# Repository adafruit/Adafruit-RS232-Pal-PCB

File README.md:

## Adafruit RS232 Pal - Two Channel UART to RS-232 Level Shifters - MAX3232E PCB

<a href="http://www.adafruit.com/products/5987"><br/>
Click here to purchase one from the Adafruit shop</a>

PCB files for the Adafruit RS232 Pal - Two Channel UART to RS-232 Level Shifters - MAX3232E. 

Format is EagleCAD schematic and board layout
* https://www.adafruit.com/product/5987

### Description

If you're looking to interface with telco, retro or industrial equipment you'll probably run into RS-232 interfaces. The Adafruit RS232 Pal - Two Channel UART to RS-232 Level Shifters is your friend in such cases, giving you two duplex channels of level shifting and taking care of the high/negative voltage generation all in a low cost breakout board. We use the trusty MAX3232E, a classic chip that is part of the MAX232 lineage so you know it will work great for all your RS-232 needs, up to 250Kbps.

RS-232 is what we had before USB: a 9 or 25 pin D-Sub connector that would allow data plus flow control lines. Many folks may remember these interfaces were used for mice, modems, barcode scanners, tele-types and more. We still find devices sold that have RS-232 ports, although many folks use a USB to RS-232 adapter these days.

If you want to use a microcontroller or microcomputer to chat with a RS-232 then thankfully all you need is a serial port / UART (something just about any microcontroller has) and a level shifter. The level shifter is required because while most UARTs are 0-3.3V or 0-5V logic level, RS-232 requires +-6 to +-10V, yep the signal voltage goes negative! That means a specialized shifter is required, one that can generate the extra high and low voltages and also safely convert the logic levels.

Sure you could buy a raw MAX232 chip and wire up the necessary capacitors, but this board does it all for you plus it can run on 3.3V power and logic, which many older chips can't do. It also can do 2 duplex channels, so you can have both RX and TX plus two flow control pins like RTS and CTS.

This breakout comes fully assembled with a UART side for low voltage power/logic level and an RS-232 side for high voltage signals plus the doubled and negative voltage rails in case you need to reference them. We also include a bit of header so you can solder it to a breadboard in a few minutes.

### License

Adafruit invests time and resources providing this open source design, please support Adafruit and open-source hardware by purchasing products from [Adafruit](https://www.adafruit.com)!

Designed by Limor Fried/Ladyada for Adafruit Industries.

Creative Commons Attribution/Share-Alike, all text above must be included in any redistribution. 
See license.txt for additional details.

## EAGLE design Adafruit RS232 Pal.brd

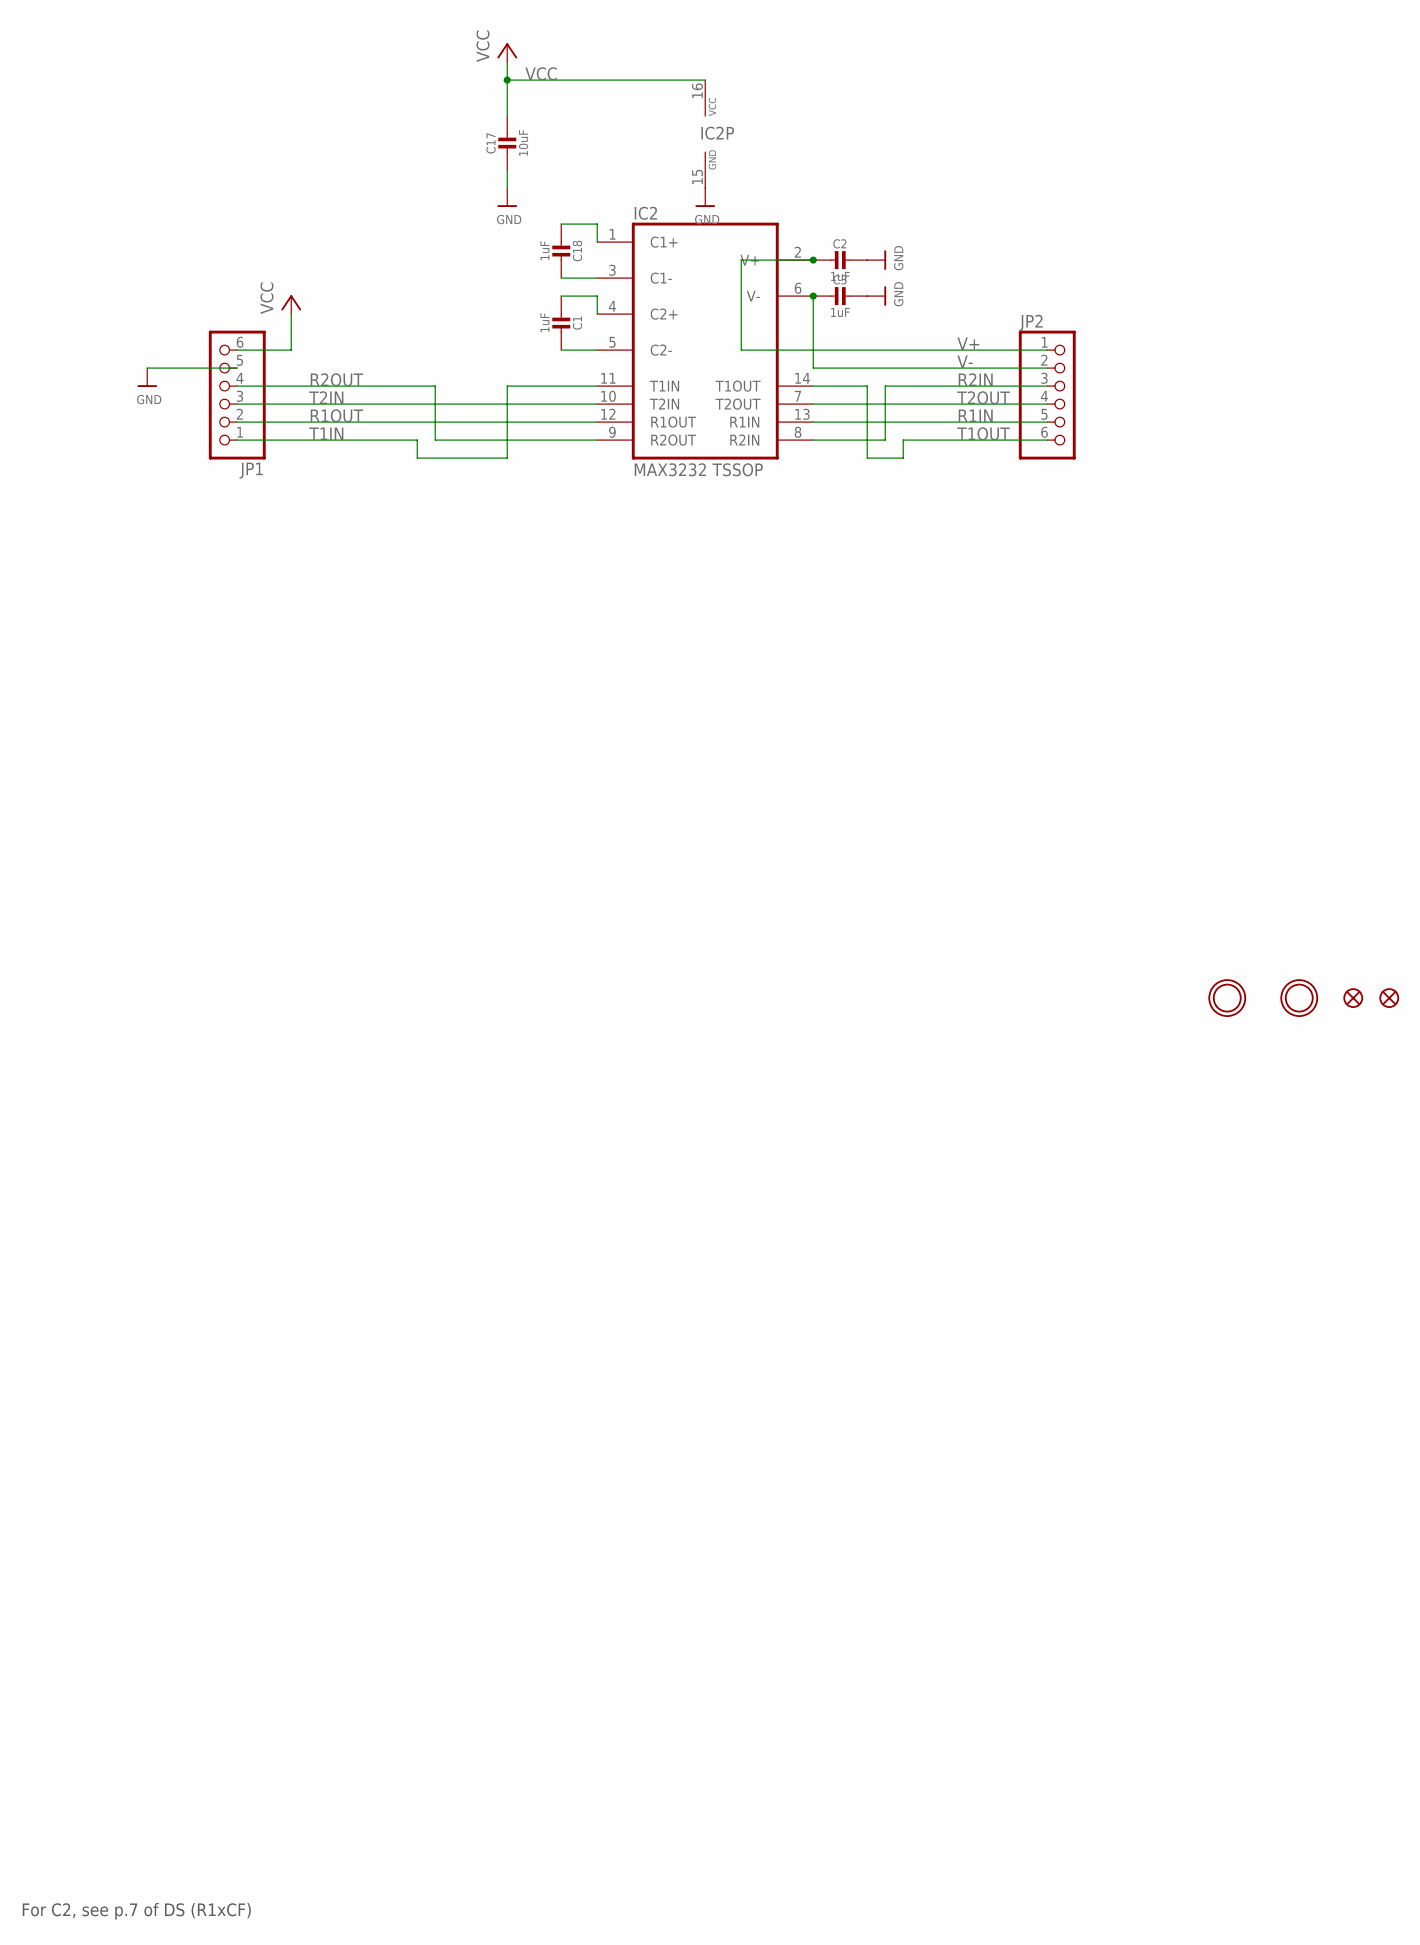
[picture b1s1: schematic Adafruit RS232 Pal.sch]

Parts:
C1, C2, C3, C18: 1uF; 0603-NO
C17: 10uF; 0805-NO
FID1, FID2: FIDUCIAL_0.5MM
IC2: MAX3232 TSSOP; TSSOP16
JP1, JP2: HEADER-1X670MIL; 1X06_ROUND_70
U$2, U$3: MOUNTINGHOLE2.5; MOUNTINGHOLE_2.5_PLATED

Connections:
GND: C2.1, C3.1, C17.2, IC2.15 (GND), JP1.5
unnamed: C18.2, IC2.1 (C1+)
unnamed: C18.1, IC2.3 (C1-)
unnamed: C1.1, IC2.5 (C2-)
unnamed: C1.2, IC2.4 (C2+)
R1IN: IC2.13 (R1IN), JP2.5
R1OUT: IC2.12 (R1OUT), JP1.2
R2IN: IC2.8 (R2IN), JP2.3
R2OUT: IC2.9 (R2OUT), JP1.4
T1IN: IC2.11 (T1IN), JP1.1
T1OUT: IC2.14 (T1OUT), JP2.6
T2IN: IC2.10 (T2IN), JP1.3
T2OUT: IC2.7 (T2OUT), JP2.4
V+: C2.2, IC2.2 (V+), JP2.1
V-: C3.2, IC2.6 (V-), JP2.2
VCC: C17.1, IC2.16 (VCC), JP1.6

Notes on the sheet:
For C2, see p.7 of DS (R1xCF)

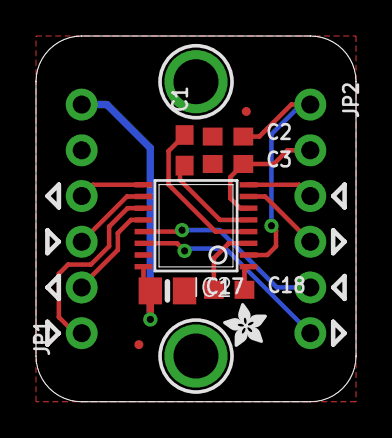
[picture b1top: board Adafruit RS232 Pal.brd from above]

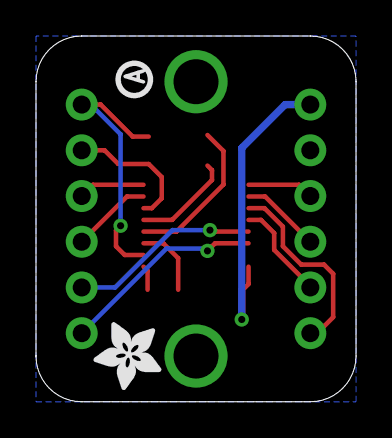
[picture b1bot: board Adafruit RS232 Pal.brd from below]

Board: 2 copper layers, 17.8 x 20.3 mm, 33 parts (4 on the bottom side), 16 nets.

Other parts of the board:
PLABEL0: PLABEL0
PLABEL1: PLABEL1
PLABEL2: PLABEL2
PLABEL3: PLABEL3
PLABEL4: PLABEL4
PLABEL5: PLABEL5
PLABEL6: PLABEL6
PLABEL7: PLABEL7
PLABEL8: PLABEL8
PLABEL9: PLABEL9
PLABEL10: PLABEL10
PLABEL11: PLABEL11
PLABEL12: PLABEL12
PLABEL13: PLABEL13
PLABEL14: PLABEL14
PLABEL15: PLABEL15
PLABEL16: PLABEL16
PLABEL17: PLABEL17
U$5: PCBFEAT-REV-040
U$8: ADAFRUIT_3.5MM
U$9: ADAFRUIT_2.5MM

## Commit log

2024-07-08 cookiecutter

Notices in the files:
parts and their libraries:
microbuilder: This work is placed in the public domain, and may be freely used for commercial and non-commercial work with the following conditions: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
